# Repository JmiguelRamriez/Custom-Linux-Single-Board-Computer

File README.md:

# Custom Linux Single Board Computer

Open-source hardware design for a minimal **Allwinner V3s**-based Single Board Computer, designed with **KiCad 9.0**.

## Features

- **Allwinner V3s** — ARM Cortex-A7 @ 1.2 GHz with **64 MB integrated DDR2 RAM** (SiP)
- **EA3036CQB** PMIC — 3-channel regulator (1.2V / 1.8V / 3.3V) from 5V input
- **10/100 Ethernet** — integrated PHY in V3s + RJ45 with magnetics (Hanrun HR911105A)
- **USB Type-C** — power input (5V) and USB OTG
- **USB Type-A** — host port
- **microSD** card slot (Molex 104031-0811, push-push) — boot and storage
- **Debug UART** — 3-pin 2.54mm header for serial console
- **GPIO header** — 2x20 pin, Raspberry Pi-like pinout
- **CR1220** coin cell holder — RTC backup
- **Boot/reset button**

## Pinout (J6 — 40-pin GPIO Header)

```
         +3.3V  (1)  (2)  +5V
     UART2_TX  (3)  (4)  +5V
     UART2_RX  (5)  (6)  GND
     I2C0_SCL  (7)  (8)  PWM0
     I2C0_SDA  (9) (10)  PWM1
    SPI0_MISO (11) (12)  GPIO_PE2
     SPI0_CLK (13) (14)  GND
      SPI0_CS (15) (16)  GPIO_PE4
    SPI0_MOSI (17) (18)  GPIO_PE6
    GPIO_PE0  (19) (20)  GND
         +3.3V (21) (22) GPIO_PE8
    GPIO_PE1  (23) (24)  GPIO_PE10
          GND (25) (26)  GPIO_PE12
    GPIO_PE3  (27) (28)  GPIO_PE14
    GPIO_PE5  (29) (30)  GND
    GPIO_PE7  (31) (32)  GPIO_PE15
    GPIO_PE9  (33) (34)  GND
    GPIO_PE11 (35) (36)  GPIO_PE16
    GPIO_PE13 (37) (38)  GPIO_PE17
          GND (39) (40)  +1V8
```

## Gallery

### PCB Layout

### 3D View

### Schematic

## Board Specifications

| Parameter | Value |
|-----------|-------|
| Layers | 4 |
| Dimensions | 115.6 × 61.2 mm |
| PCB thickness | 1.6 mm |
| Copper finish | ENIG (gold) |
| Min track width | 0.15 mm |
| Min clearance | 0.15 mm |
| Via size | 0.6 mm / 0.3 mm drill |

## Repository Contents

| File / Folder | Description |
|---------------|-------------|
| `Allwinner V3s.kicad_sch` | Schematic |
| `Allwinner V3s.kicad_pcb` | PCB layout |
| `Allwinner V3s.kicad_pro` | KiCad project file |
| `production/` | Gerbers, BOM, pick-and-place, netlist |
| `Allwinner V3s-backups/` | Design backups |

## Production Files

The `production/` folder contains everything needed for PCB fabrication and assembly:

- `Allwinner_V3s.zip` — Gerber files + NC drill
- `bom.csv` — Bill of Materials with LCSC part numbers
- `positions.csv` — Pick-and-place centroid data
- `netlist.ipc` — IPC-356 electrical test netlist

## Datasheets

| Component | Datasheet |
|-----------|-----------|
| Allwinner V3s | [V3s Datasheet V1.0](https://linux-sunxi.org/images/2/23/Allwinner_V3s_Datasheet_V1.0.pdf) |
| EA3036C (PMIC) | [EA3036C datasheet](https://www.lcsc.com/datasheet/C570857.pdf) |
| HR911105A (RJ45) | [HR911105A specification](https://www.shotech.de/Datasheet/HanRun/1811141815_HANRUN-Zhongshan-HanRun-Elec-HR911105A_C12074.pdf) |

## Status

- **DRC**: 1 warning (local footprint override, non-critical)

## License

Open hardware — use, modify, and manufacture at your own risk.

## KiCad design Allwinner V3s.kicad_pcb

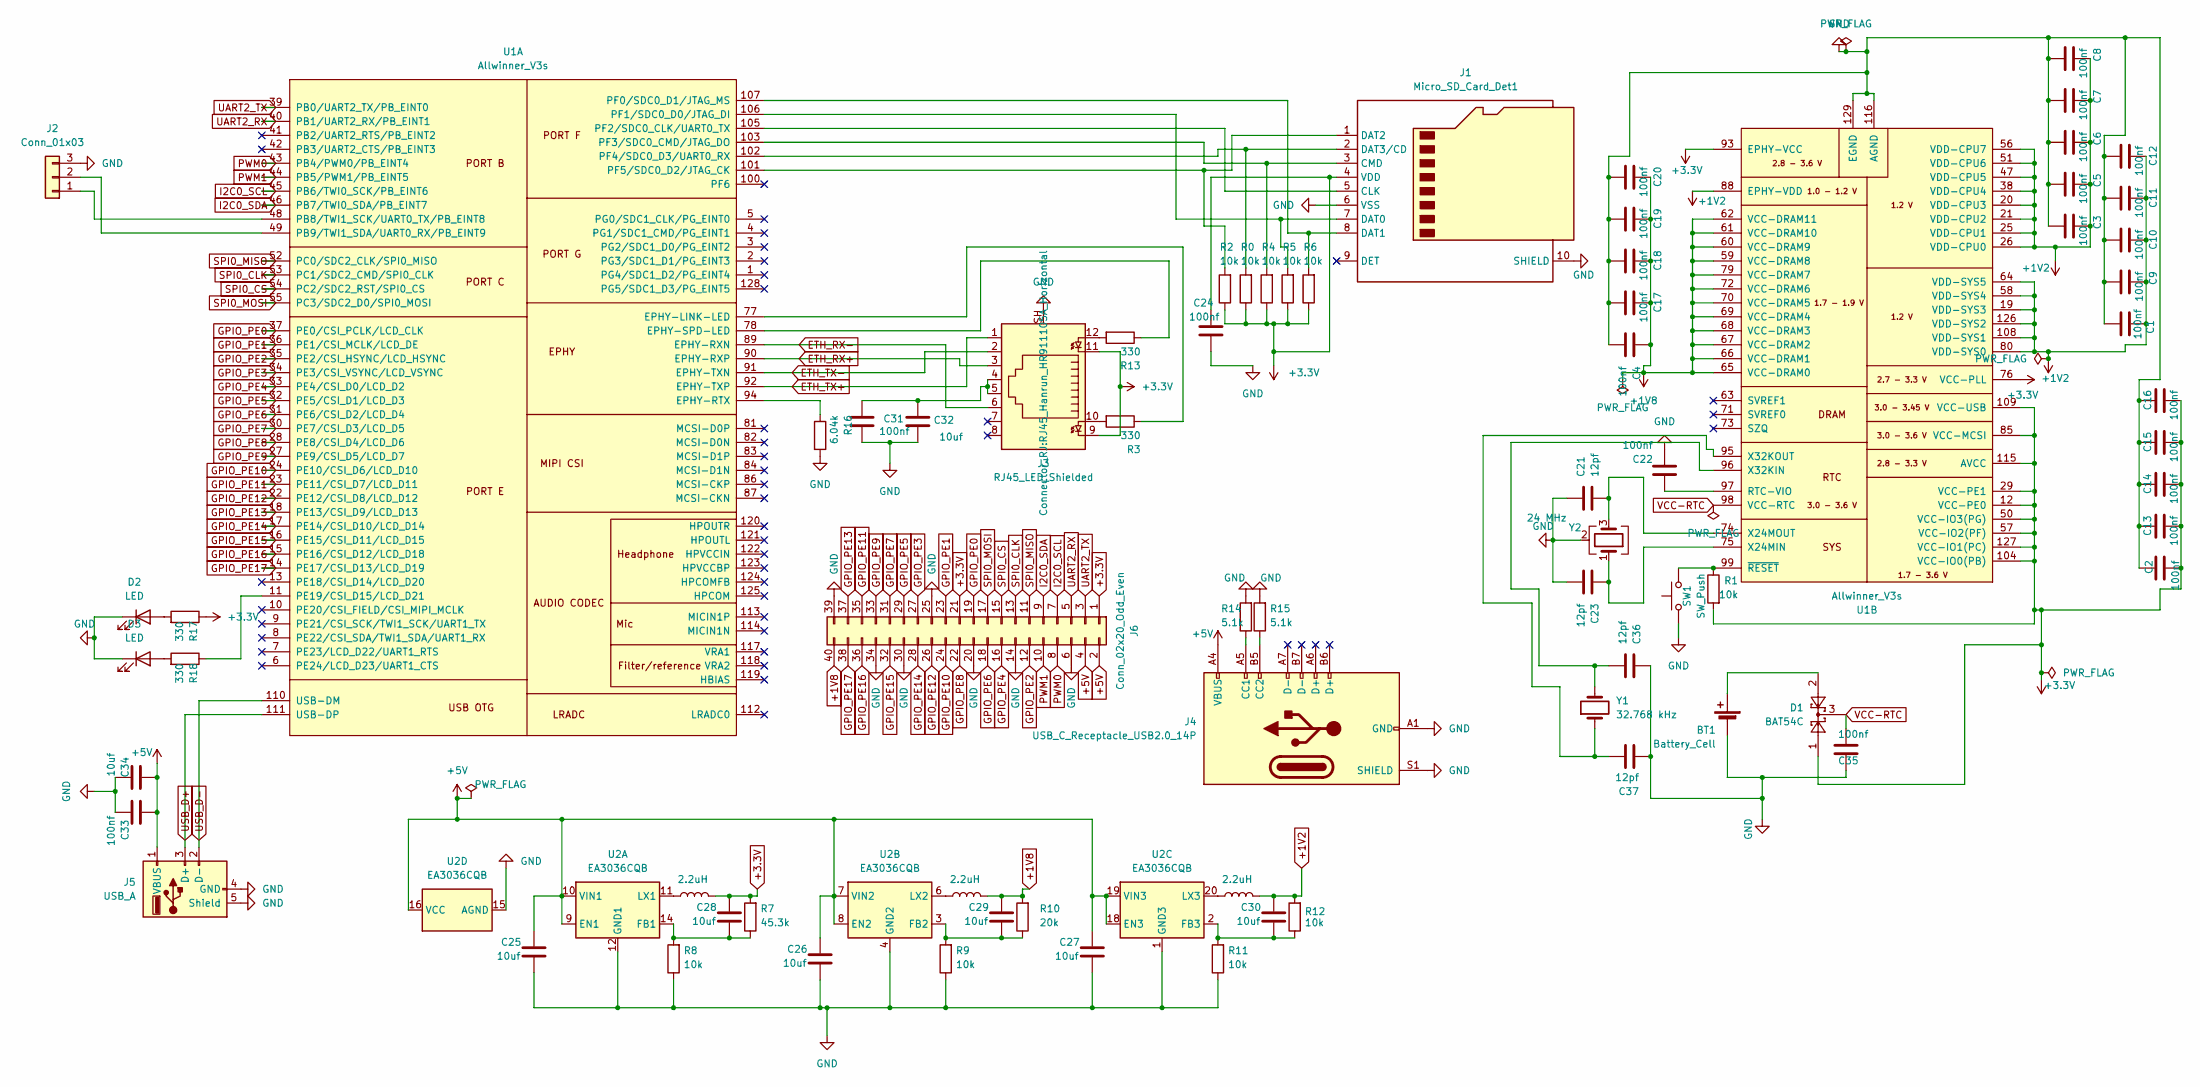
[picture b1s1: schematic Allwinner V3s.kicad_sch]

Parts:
BT1: Battery_Cell; BatteryHolder_Keystone_3000_1x12mm
C1, C2, C3, C4, C5, C6, C7, C8, C9, C10, C11, C12, C13, C14, C15, C16, C17, C18, C19, C20, C22, C24, C31, C33, C35: 100nf; C_0603_1608Metric
C21, C23: 12pf; C_0603_1608Metric
C25, C26, C27, C28, C29, C30, C32, C34: 10uf; C_0603_1608Metric
C36, C37: 12pf; C_0402_1005Metric
D1: BAT54C; SOT-23
D2, D3: LED; LED_0805_2012Metric
J1: Micro_SD_Card_Det1; microSD_HC_Molex_104031-0811
J2: Conn_01x03; PinHeader_1x03_P2.54mm_Vertical
J3: RJ45_LED_Shielded; RJ45_Hanrun_HR911105A_Horizontal
J4: USB_C_Receptacle_USB2.0_14P; USB_C_Receptacle_HRO_TYPE-C-31-M-17
J5: USB_A; USB_A_Molex_67643_Horizontal
J6: Conn_02x20_Odd_Even; PinHeader_2x20_P2.54mm_Vertical
L1, L2, L3: 2.2uH; L_0805_2012Metric
R0, R1, R2, R4, R5, R6, R8, R9, R11, R12: 10k; R_0603_1608Metric
R3, R13, R17, R18: 330; R_0603_1608Metric
R7: 45.3k; R_0603_1608Metric
R10: 20k; R_0603_1608Metric
R14, R15: 5.1k; R_0603_1608Metric
R16: 6.04k; R_0603_1608Metric
SW1: SW_Push; SW_Push_1P1T_NO_CK_KMR2
U1: Allwinner_V3s; eLQFP-128_14x14_Pitch0.4mm_EPAD_5.72mm; LCSC C9900008288
U2: EA3036CQB; QFN-20-1EP_3x3mm_P0.4mm_EP1.65x1.65mm
Y1: 32.768 kHz; Crystal_SMD_3215-2Pin_3.2x1.5mm
Y2: 24 MHz; Crystal_SMD_3225-4Pin_3.2x2.5mm

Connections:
+1V2: C1.1, C3.1, C5.1, C6.1, C7.1, C8.1, C9.1, C10.1, C11.1, C12.1, C30.1, L3.2, R12.2, U1.19 (VDD-SYS3), U1.20 (VDD-CPU3), U1.21 (VDD-CPU2), U1.25 (VDD-CPU1), U1.26 (VDD-CPU0), U1.38 (VDD-CPU4), U1.47 (VDD-CPU5), U1.51 (VDD-CPU6), U1.56 (VDD-CPU7), U1.58 (VDD-SYS4), U1.64 (VDD-SYS5), U1.80 (VDD-SYS0), U1.88 (EPHY-VDD), U1.108 (VDD-SYS1), U1.126 (VDD-SYS2)
+1V8: C4.1, C17.1, C18.1, C19.1, C20.1, C29.1, J6.40, L2.2, R10.2, U1.59 (VCC-DRAM8), U1.60 (VCC-DRAM9), U1.61 (VCC-DRAM10), U1.62 (VCC-DRAM11), U1.65 (VCC-DRAM0), U1.66 (VCC-DRAM1), U1.67 (VCC-DRAM2), U1.68 (VCC-DRAM3), U1.69 (VCC-DRAM4), U1.70 (VCC-DRAM5), U1.72 (VCC-DRAM6), U1.79 (VCC-DRAM7)
+3.3V: C2.1, C13.1, C14.1, C15.1, C16.1, C24.1, C28.1, D1.1, J1.4 (VDD), J3.9, J3.11, J6.1, J6.21, L1.2, R0.1, R1.2, R2.1, R4.1, R5.1, R6.1, R7.2, R17.1, U1.12 (VCC-PE0), U1.29 (VCC-PE1), U1.50 (VCC-IO3(PG)), U1.57 (VCC-IO2(PF)), U1.76 (VCC-PLL), U1.85 (VCC-MCSI), U1.93 (EPHY-VCC), U1.104 (VCC-IO0(PB)), U1.109 (VCC-USB), U1.115 (AVCC), U1.127 (VCC-IO1(PC))
+5V: C25.1, C26.1, C27.1, C33.2, C34.2, J4.A4 (VBUS), J4.A9 (VBUS), J4.B4 (VBUS), J4.B9 (VBUS), J5.1 (VBUS), J6.2, J6.4, U2.7 (VIN2), U2.8 (EN2), U2.9 (EN1), U2.10 (VIN1), U2.16 (VCC), U2.18 (EN3), U2.19 (VIN3)
ETH_RX+: J3.3, U1.90 (EPHY-RXP)
ETH_RX-: J3.6, U1.89 (EPHY-RXN)
ETH_TX+: J3.1, U1.92 (EPHY-TXP)
ETH_TX-: J3.2, U1.91 (EPHY-TXN)
GND: BT1.2 (-), C1.2, C2.2, C3.2, C4.2, C5.2, C6.2, C7.2, C8.2, C9.2, C10.2, C11.2, C12.2, C13.2, C14.2, C15.2, C16.2, C17.2, C18.2, C19.2, C20.2, C21.1, C22.2, C23.2, C24.2, C25.2, C26.2, C27.2, C31.1, C32.1, C33.1, C34.1, C35.2, C36.1, C37.2, D2.1 (K), D3.1 (K), J1.6 (VSS), J1.10 (SHIELD), J2.3, J3.SH, J4.A1 (GND), J4.A12 (GND), J4.B1 (GND), J4.B12 (GND), J4.S1 (SHIELD), J5.4 (GND), J5.5 (Shield), J6.6, J6.14, J6.20, J6.25, J6.30, J6.34, J6.39, R8.1, R9.1, R11.1, R14.2, R15.2, R16.2, SW1.1, U1.116 (AGND), U1.129 (EGND), U2.1 (GND3), U2.4 (GND2), U2.5 (GND2), U2.12 (GND1), U2.13 (GND1), U2.15 (AGND), U2.17 (AGND), U2.21 (AGND), Y2.2 (G), Y2.4 (G)
GPIO_PE0: J6.19, U1.37 (PE0/CSI_PCLK/LCD_CLK)
GPIO_PE1: J6.23, U1.36 (PE1/CSI_MCLK/LCD_DE)
GPIO_PE2: J6.12, U1.35 (PE2/CSI_HSYNC/LCD_HSYNC)
GPIO_PE3: J6.27, U1.34 (PE3/CSI_VSYNC/LCD_VSYNC)
GPIO_PE4: J6.16, U1.33 (PE4/CSI_D0/LCD_D2)
GPIO_PE5: J6.29, U1.32 (PE5/CSI_D1/LCD_D3)
GPIO_PE6: J6.18, U1.31 (PE6/CSI_D2/LCD_D4)
GPIO_PE7: J6.31, U1.30 (PE7/CSI_D3/LCD_D5)
GPIO_PE8: J6.22, U1.28 (PE8/CSI_D4/LCD_D6)
GPIO_PE9: J6.33, U1.27 (PE9/CSI_D5/LCD_D7)
GPIO_PE10: J6.24, U1.24 (PE10/CSI_D6/LCD_D10)
GPIO_PE11: J6.35, U1.23 (PE11/CSI_D7/LCD_D11)
GPIO_PE12: J6.26, U1.22 (PE12/CSI_D8/LCD_D12)
GPIO_PE13: J6.37, U1.18 (PE13/CSI_D9/LCD_D13)
GPIO_PE14: J6.28, U1.17 (PE14/CSI_D10/LCD_D14)
GPIO_PE15: J6.32, U1.16 (PE15/CSI_D11/LCD_D15)
GPIO_PE16: J6.36, U1.15 (PE16/CSI_D12/LCD_D18)
GPIO_PE17: J6.38, U1.14 (PE17/CSI_D13/LCD_D19)
I2C0_SCL: J6.7, U1.45 (PB6/TWI0_SCK/PB_EINT6)
I2C0_SDA: J6.9, U1.46 (PB7/TWI0_SDA/PB_EINT7)
unnamed: BT1.1 (+), D1.2
unnamed: C31.2, C32.2, J3.4, J3.5
unnamed: D2.2 (A), R17.2
unnamed: D3.2 (A), R18.2
unnamed: J1.5 (CLK), U1.105 (PF2/SDC0_CLK/UART0_TX)
unnamed: J1.3 (CMD), R4.2, U1.103 (PF3/SDC0_CMD/JTAG_DO)
unnamed: J1.7 (DAT0), R5.2, U1.106 (PF1/SDC0_D0/JTAG_DI)
unnamed: J1.8 (DAT1), R6.2, U1.107 (PF0/SDC0_D1/JTAG_MS)
unnamed: J1.1 (DAT2), R2.2, U1.101 (PF5/SDC0_D2/JTAG_CK)
unnamed: J1.2 (DAT3/CD), R0.2, U1.102 (PF4/SDC0_D3/UART0_RX)
unnamed: J2.1, U1.48 (PB8/TWI1_SCK/UART0_TX/PB_EINT8)
unnamed: J2.2, U1.49 (PB9/TWI1_SDA/UART0_RX/PB_EINT9)
unnamed: J3.10, R3.2
unnamed: J3.12, R13.2
unnamed: J4.A5 (CC1), R14.1
unnamed: J4.B5 (CC2), R15.1
unnamed: R3.1, U1.77 (EPHY-LINK-LED)
unnamed: R16.1, U1.94 (EPHY-RTX)
unnamed: R13.1, U1.78 (EPHY-SPD-LED)
unnamed: R18.1, U1.11 (PE19/CSI_D15/LCD_D21)
unnamed: C22.1, U1.97 (RTC-VIO)
unnamed: C23.1, U1.75 (X24MIN), Y2.1
unnamed: C21.2, U1.74 (X24MOUT), Y2.3
unnamed: C36.2, U1.96 (X32KIN), Y1.2
unnamed: C37.1, U1.95 (X32KOUT), Y1.1
unnamed: R1.1, SW1.2, U1.99 (~RESET)
unnamed: C28.2, R7.1, R8.2, U2.14 (FB1)
unnamed: L1.1, U2.11 (LX1)
unnamed: C29.2, R9.2, R10.1, U2.3 (FB2)
unnamed: L2.1, U2.6 (LX2)
unnamed: C30.2, R11.2, R12.1, U2.2 (FB3)
unnamed: L3.1, U2.20 (LX3)
PWM0: J6.8, U1.43 (PB4/PWM0/PB_EINT4)
PWM1: J6.10, U1.44 (PB5/PWM1/PB_EINT5)
SPI0_CLK: J6.13, U1.53 (PC1/SDC2_CMD/SPI0_CLK)
SPI0_CS: J6.15, U1.54 (PC2/SDC2_RST/SPI0_CS)
SPI0_MISO: J6.11, U1.52 (PC0/SDC2_CLK/SPI0_MISO)
SPI0_MOSI: J6.17, U1.55 (PC3/SDC2_D0/SPI0_MOSI)
UART2_RX: J6.5, U1.40 (PB1/UART2_RX/PB_EINT1)
UART2_TX: J6.3, U1.39 (PB0/UART2_TX/PB_EINT0)
USB_D+: J5.3 (D+), U1.111 (USB-DP)
USB_D-: J5.2 (D-), U1.110 (USB-DM)
VCC-RTC: C35.1, D1.3, U1.98 (VCC-RTC)

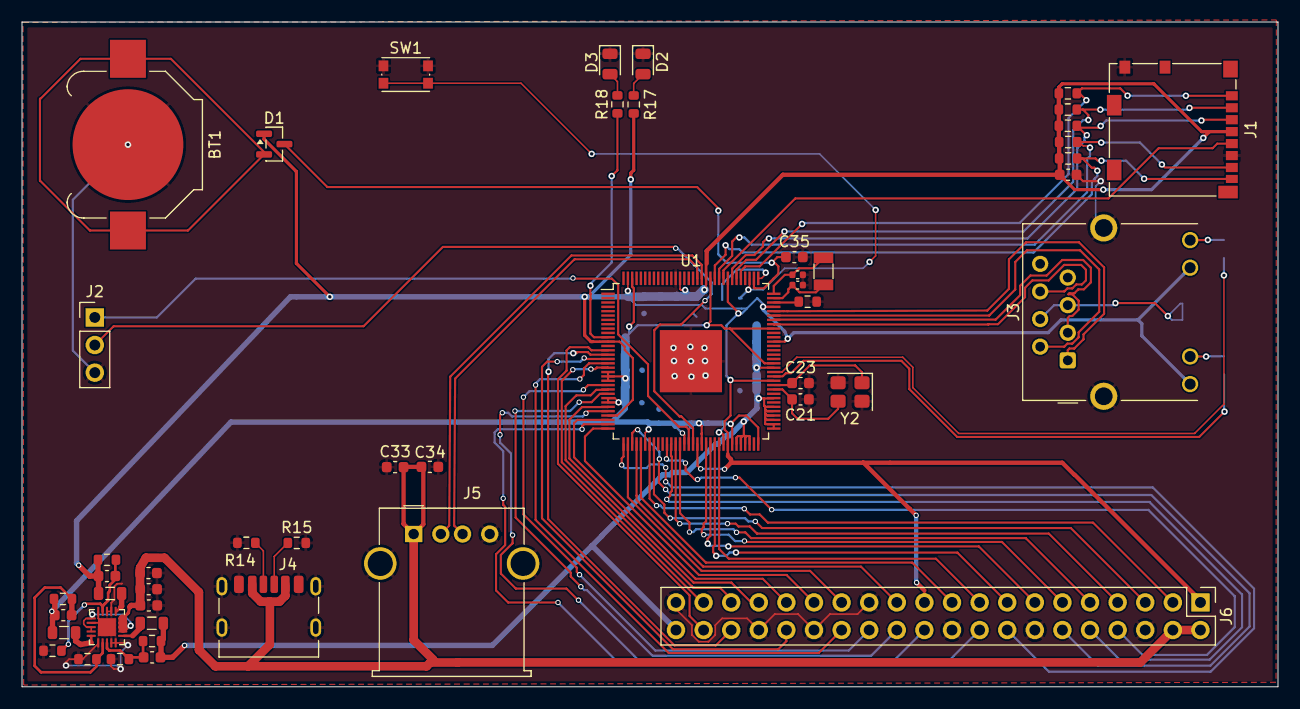
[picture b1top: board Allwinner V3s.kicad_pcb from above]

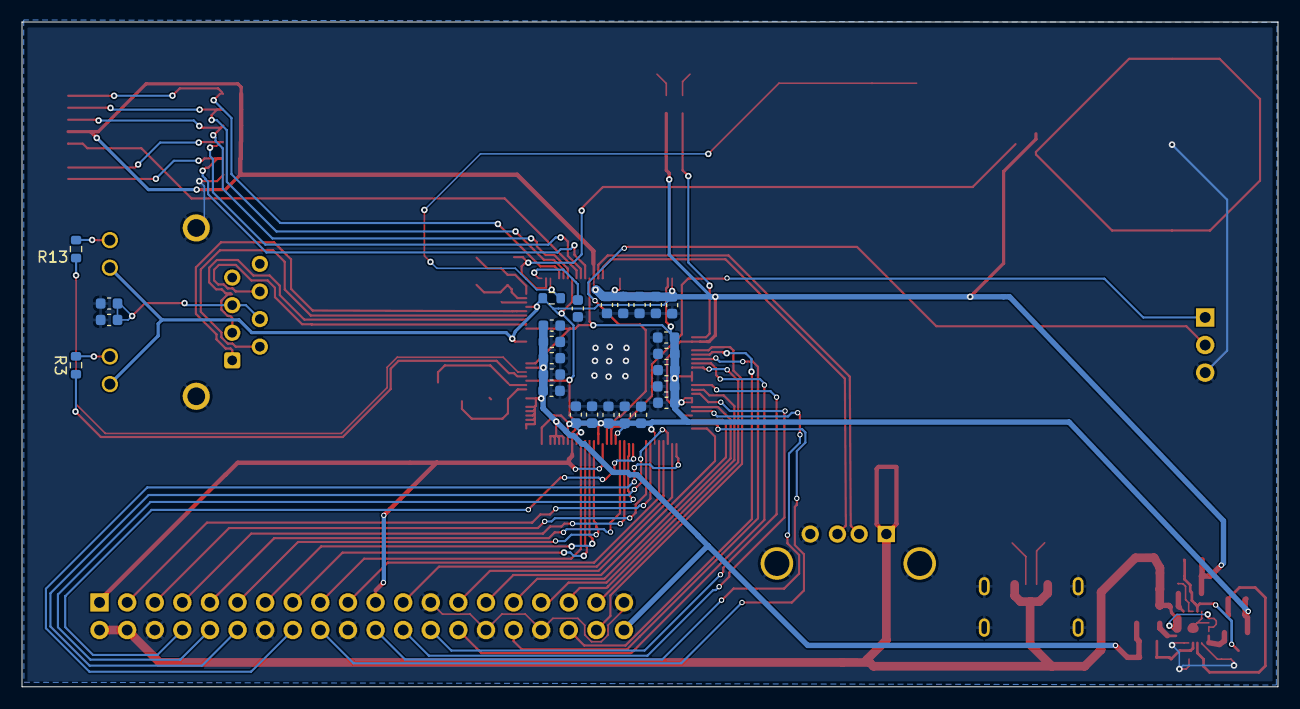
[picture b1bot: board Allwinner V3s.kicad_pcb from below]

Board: 4 copper layers, 115.6 x 61.2 mm, 74 parts (26 on the bottom side), 72 nets.

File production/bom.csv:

Designator,Footprint,Quantity,Value,LCSC Part #
BT1,BatteryHolder_Keystone_3000_1x12mm,1,Battery_Cell,C238097
"C1, C10, C11, C12, C13, C14, C15, C16, C17, C18, C19, C2, C20, C22, C24, C3, C31, C33, C35, C4, C5, C6, C7, C8, C9",0603,25,100nf,C129621
"C21, C23",0603,2,12pf,C107034
"C25, C26, C27, C28, C29, C30, C32, C34",0603,8,10uF,C38898
"C36, C37",0402,2,12pf,C1547
D1,SOT-23,1,BAT54C,C2135
"D2, D3",0805,2,LED,C84256
J1,microSD_HC_Molex_104031-0811,1,Micro_SD_Card_Det1,C585350
J2,PinHeader_1x03_P2.54mm_Vertical,1,Conn_01x03,C49257
J3,RJ45_Hanrun_HR911105A_Horizontal,1,RJ45_LED_Shielded,C12074
J4,USB_C_Receptacle_HRO_TYPE-C-31-M-17,1,USB_C_Receptacle_USB2.0_14P,C165948
J5,USB_A_Molex_67643_Horizontal,1,USB_A,C2765194
J6,PinHeader_2x20_P2.54mm_Vertical,1,Conn_02x20_Odd_Even,C50980
"L1, L2, L3",0805,3,2.2uH,C341781
"R0, R1, R11, R12, R2, R4, R5, R6, R8, R9",0603,10,10k,C99198
R10,0603,1,20k,C105575
"R13, R17, R18, R3",0603,4,330,C105879
"R14, R15",0603,2,5.1k,C3016319
R16,0603,1,6.04k,C25977
R7,0603,1,45.3k,C245971
SW1,SW_Push_1P1T_NO_CK_KMR2,1,SW_Push,C72443
U1,eLQFP-128_14x14_Pitch0.4mm_EPAD_5.72mm,1,Allwinner_V3s,C2687449
U2,QFN-20-1EP_3x3mm_P0.4mm_EP1.65x1.65mm,1,EA3036CQB,C570857
Y1,Crystal_SMD_3215-2Pin_3.2x1.5mm,1,32.768 kHz,C620155
Y2,Crystal_SMD_3225-4Pin_3.2x2.5mm,1,24 MHz,C70590
